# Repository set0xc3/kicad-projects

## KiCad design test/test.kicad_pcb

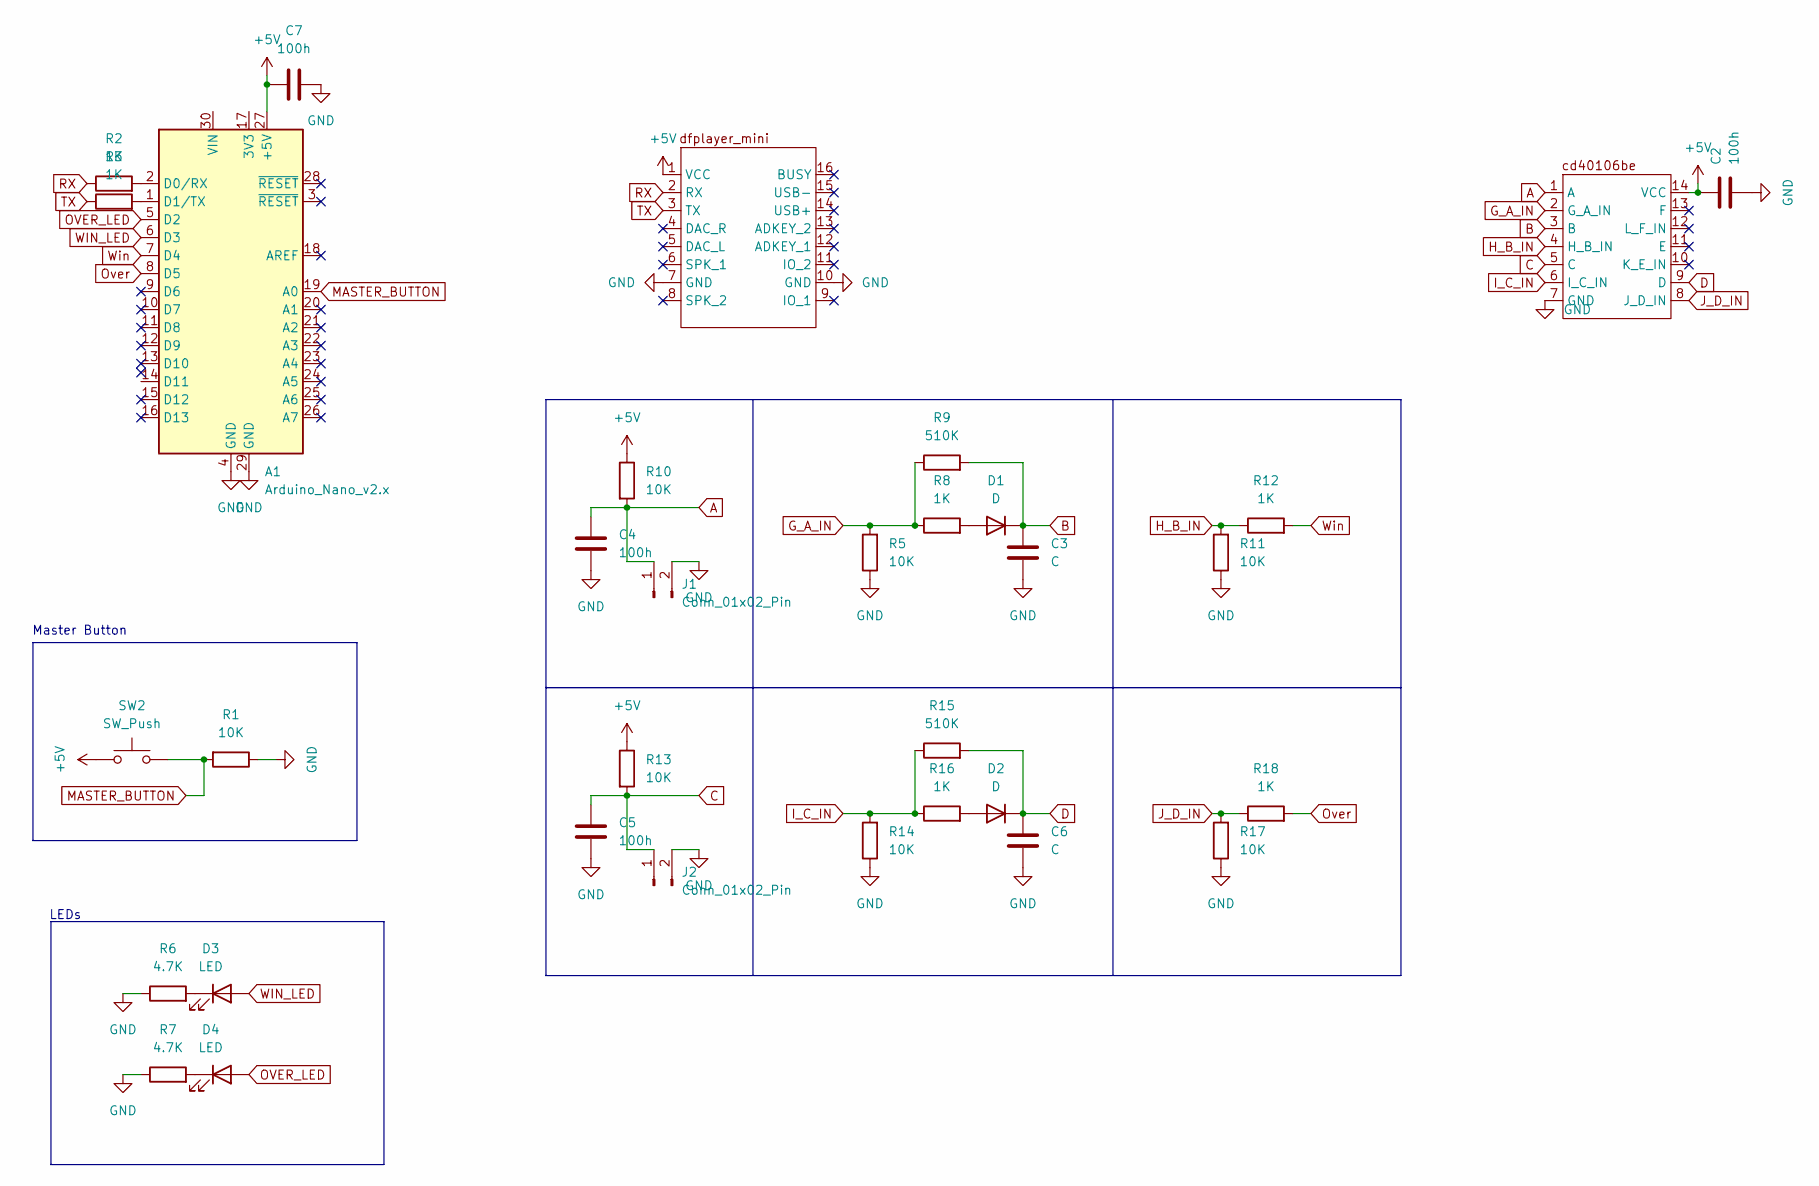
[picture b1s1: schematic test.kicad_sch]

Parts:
A1: Arduino_Nano_v2.x; Arduino_Nano
C2, C4, C5, C7: 100h; C_Disc_D3.0mm_W1.6mm_P2.50mm
C3, C6: C; C_Disc_D3.0mm_W1.6mm_P2.50mm
D1, D2: D; D_5W_P5.08mm_Vertical_AnodeUp
D3, D4: LED; LED_D3.0mm
J1, J2: Conn_01x02_Pin; PinHeader_1x02_P1.00mm_Horizontal
R1, R5, R10, R11, R13, R14, R17: 10K; R_Axial_DIN0204_L3.6mm_D1.6mm_P1.90mm_Vertical
R2, R3, R8, R12, R16, R18: 1K; R_Axial_DIN0204_L3.6mm_D1.6mm_P1.90mm_Vertical
R6, R7: 4.7K; R_Axial_DIN0204_L3.6mm_D1.6mm_P1.90mm_Vertical
R9, R15: 510K; R_Axial_DIN0204_L3.6mm_D1.6mm_P1.90mm_Vertical
SW2: SW_Push; SW_PUSH_6mm
U2: dfplayer_mini
U3: cd40106be

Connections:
+5V: A1.27 (+5V), C2.1, C7.1, R10.1, R13.1, SW2.1, U2.1 (VCC), U3.14 (VCC)
A: C4.1, J1.1, R10.2, U3.1 (A)
B: C3.1, D1.1 (K), R9.2, U3.3 (B)
C: C5.1, J2.1, R13.2, U3.5 (C)
D: C6.1, D2.1 (K), R15.2, U3.9 (D)
GND: A1.4 (GND), A1.29 (GND), C2.2, C3.2, C4.2, C5.2, C6.2, C7.2, J1.2, J2.2, R1.1, R5.1, R6.1, R7.1, R11.1, R14.1, R17.1, U2.7 (GND), U2.10 (GND), U3.7 (GND)
G_A_IN: R5.2, R8.1, R9.1, U3.2 (G_A_IN)
H_B_IN: R11.2, R12.1, U3.4 (H_B_IN)
I_C_IN: R14.2, R15.1, R16.1, U3.6 (I_C_IN)
J_D_IN: R17.2, R18.1, U3.8 (J_D_IN)
MASTER_BUTTON: A1.19 (A0), R1.2, SW2.2
unnamed: A1.2 (D0/RX), R2.2
unnamed: A1.1 (D1/TX), R3.2
unnamed: D1.2 (A), R8.2
unnamed: D2.2 (A), R16.2
unnamed: D3.1 (K), R6.2
unnamed: D4.1 (K), R7.2
OVER_LED: A1.5 (D2), D4.2 (A)
Over: A1.8 (D5), R18.2
RX: R2.1, U2.2 (RX)
TX: R3.1, U2.3 (TX)
WIN_LED: A1.6 (D3), D3.2 (A)
Win: A1.7 (D4), R12.2

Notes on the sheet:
Master Button
LEDs

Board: 2 copper layers, 33 parts (0 on the bottom side), 23 nets, no tracks yet.

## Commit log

2024-08-01 init
2024-08-01 lab/lab: backup
2025-05-15 backup
